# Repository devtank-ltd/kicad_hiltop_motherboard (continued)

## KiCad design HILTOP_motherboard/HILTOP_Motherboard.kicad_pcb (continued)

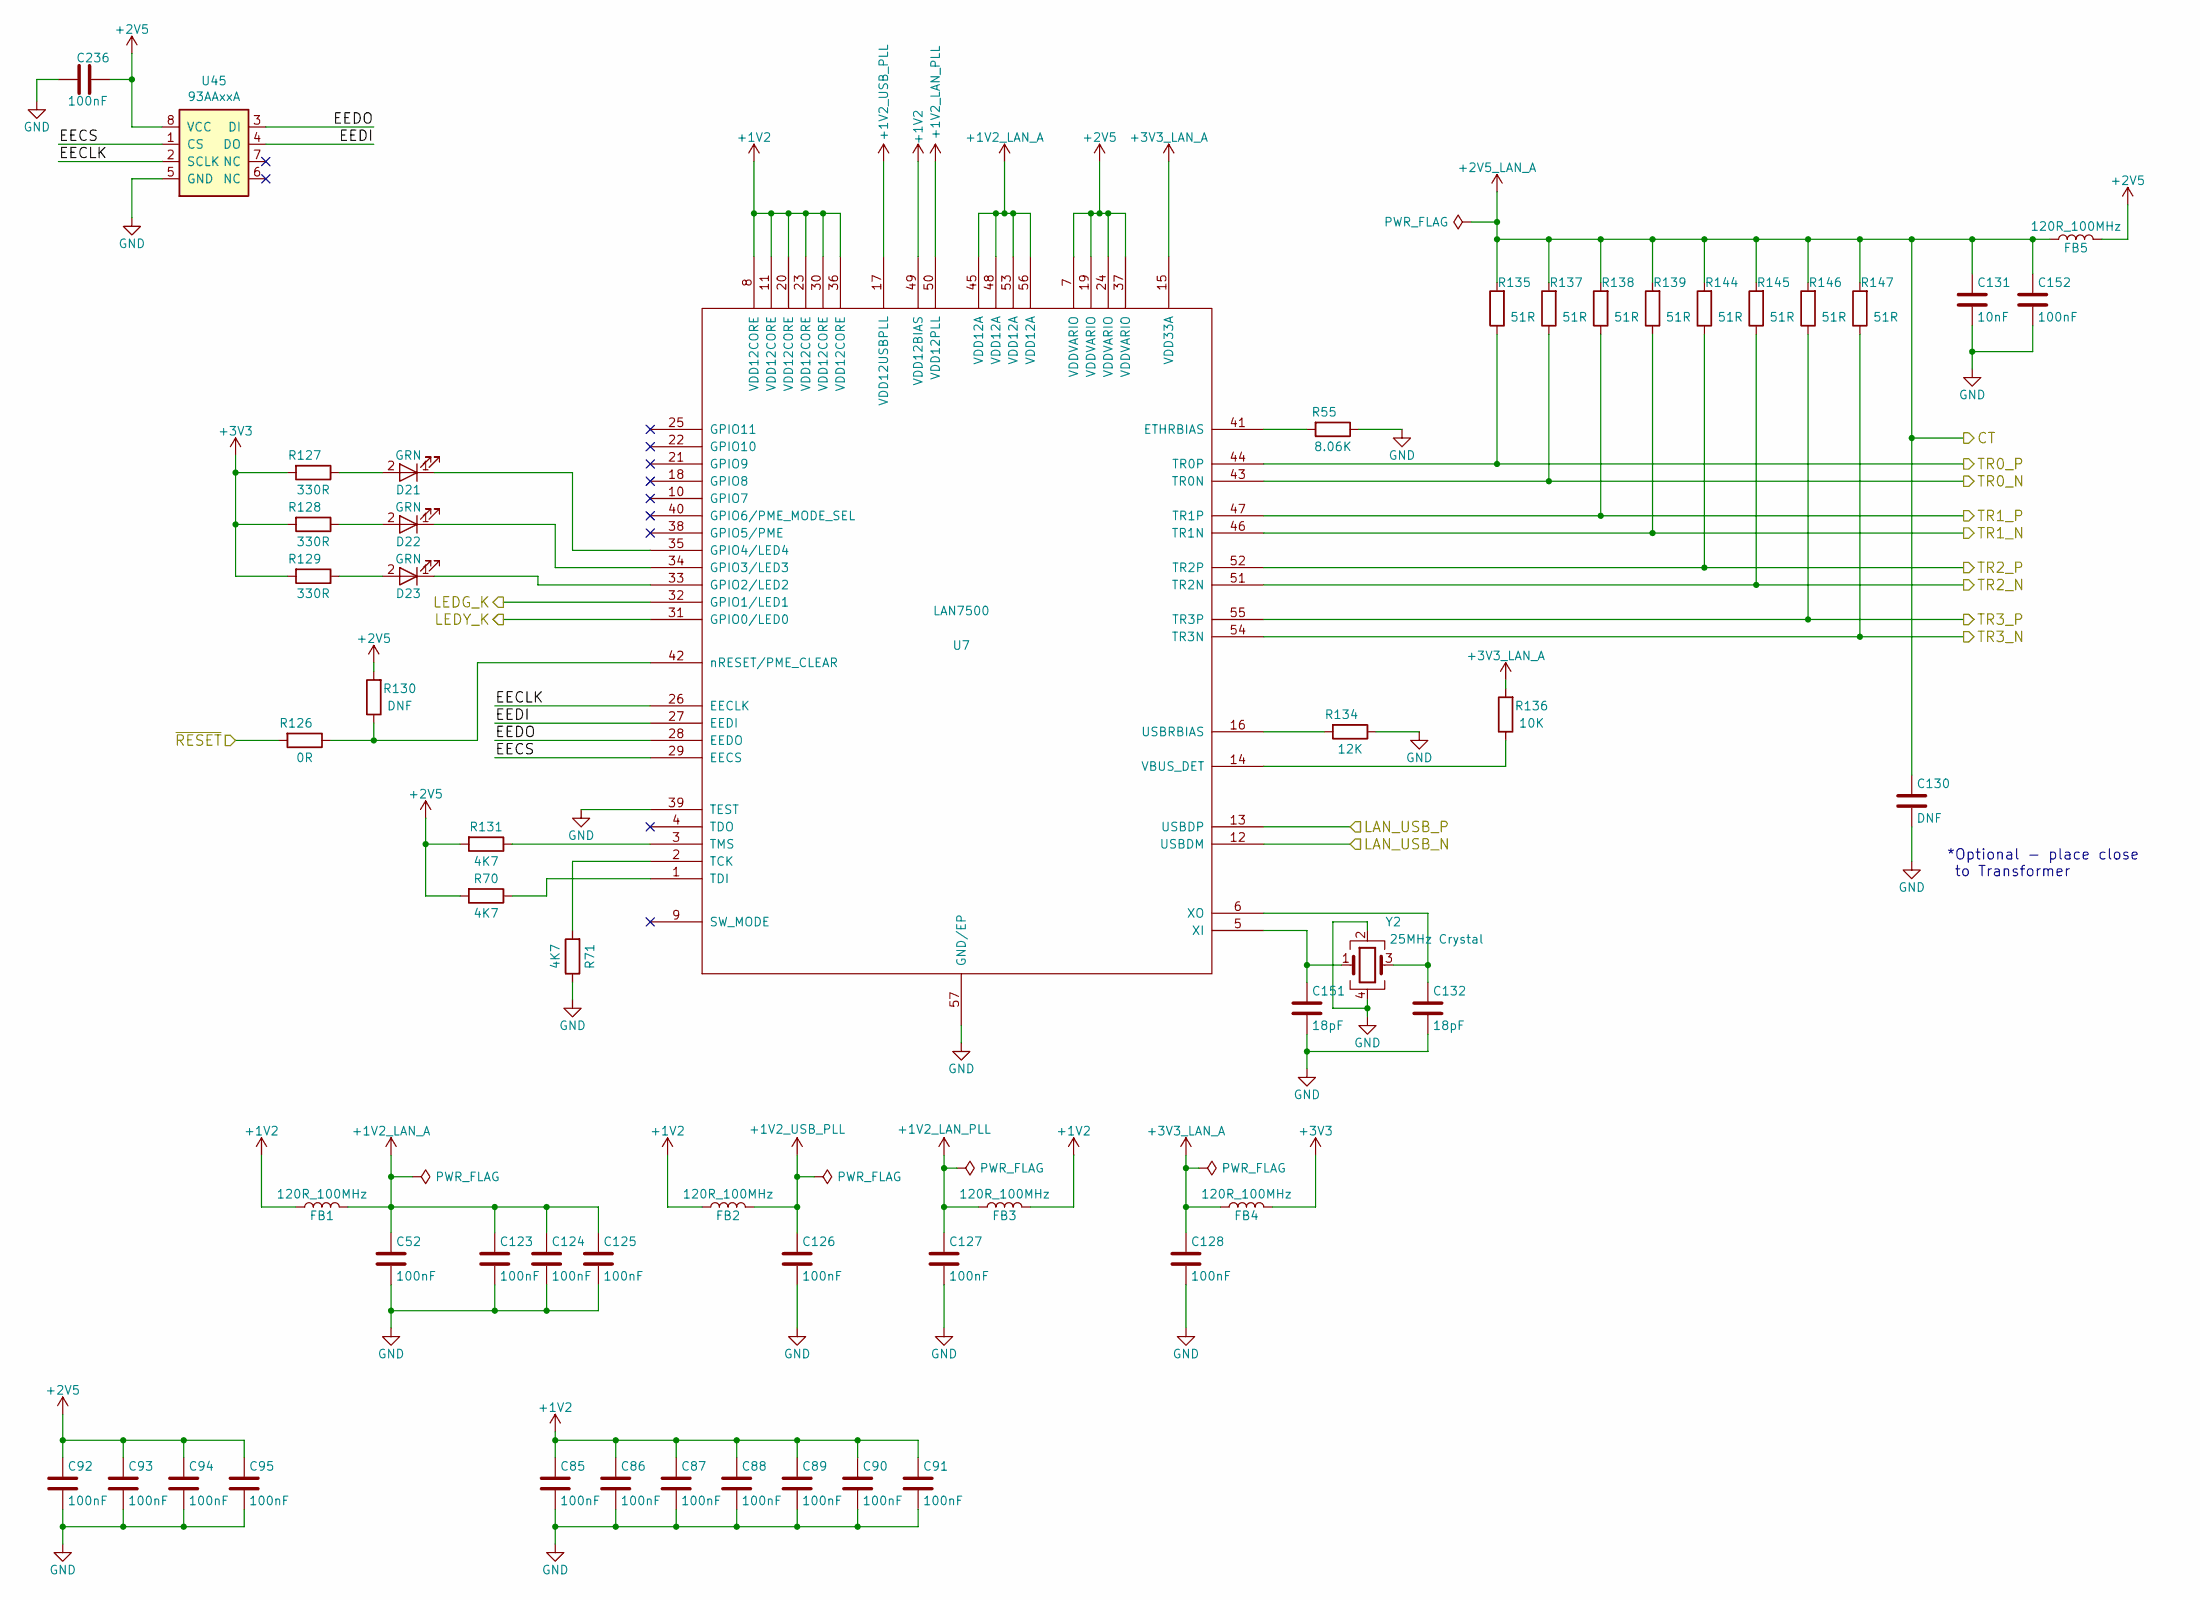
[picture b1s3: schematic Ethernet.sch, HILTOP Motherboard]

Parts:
C52: 100nF; C_0402_1005Metric
C85, C86, C87, C88, C89, C90, C91, C92, C93, C94, C95, C123, C124, C125, C126, C127, C128, C152, C236: 100nF; C_0603_1608Metric
C130: DNF; C_0603_1608Metric
C131: 10nF; C_0603_1608Metric
C132, C151: 18pF; C_0402_1005Metric
D21, D22, D23: GRN; LED_0402_1005Metric
FB1, FB2, FB3, FB4, FB5: 120R_100MHz; R_0603_1608Metric
R55: 8.06K; R_0603_1608Metric
R70, R71, R131: 4K7; R_0603_1608Metric
R126: 0R; R_0603_1608Metric
R127, R128, R129: 330R; R_0603_1608Metric
R130: DNF; R_0603_1608Metric
R134: 12K; R_0603_1608Metric
R135, R137, R138, R139, R144, R145, R146, R147: 51R; R_0603_1608Metric
R136: 10K; R_0603_1608Metric
U7: LAN7500; QFN-56_8x8mm_Pitch0.5mm
U45: 93AAxxA; SOIC-8_3.9x4.9mm_P1.27mm
Y2: 25MHz Crystal; Crystal_SMD_SeikoEpson_FA238V-4Pin_3.2x2.5mm

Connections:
+1V2: C85.1, C86.1, C87.1, C88.1, C89.1, C90.1, C91.1, FB1.1, FB2.1, FB3.2, U7.8 (VDD12CORE), U7.11 (VDD12CORE), U7.20 (VDD12CORE), U7.23 (VDD12CORE), U7.30 (VDD12CORE), U7.36 (VDD12CORE), U7.49 (VDD12BIAS); also elsewhere on the board
+1V2_LAN_A: C52.1, C123.1, C124.1, C125.1, FB1.2, U7.45 (VDD12A), U7.48 (VDD12A), U7.53 (VDD12A), U7.56 (VDD12A)
+1V2_LAN_PLL: C127.1, FB3.1, U7.50 (VDD12PLL)
+1V2_USB_PLL: C126.1, FB2.2, U7.17 (VDD12USBPLL)
+2V5: C92.1, C93.1, C94.1, C95.1, C236.1, FB5.2, R70.2, R130.2, R131.2, U7.7 (VDDVARIO), U7.19 (VDDVARIO), U7.24 (VDDVARIO), U7.37 (VDDVARIO), U45.8 (VCC); also elsewhere on the board
+2V5_LAN_A: C130.1, C131.1, C152.1, FB5.1, R135.2, R137.2, R138.2, R139.2, R144.2, R145.2, R146.2, R147.2; also elsewhere on the board
+3V3: FB4.2, R127.2, R128.2, R129.2; also elsewhere on the board
+3V3_LAN_A: C128.1, FB4.1, R136.2, U7.15 (VDD33A)
/Ethernet/EECLK: U7.26 (EECLK), U45.2 (SCLK)
/Ethernet/EECS: U7.29 (EECS), U45.1 (CS)
/Ethernet/EEDI: U7.27 (EEDI), U45.4 (DO)
/Ethernet/EEDO: U7.28 (EEDO), U45.3 (DI)
/LAN_USB_N: U7.12 (USBDM); also elsewhere on the board
/LAN_USB_P: U7.13 (USBDP); also elsewhere on the board
/LEDG_K: U7.32 (GPIO1/LED1); also elsewhere on the board
/LEDY_K: U7.31 (GPIO0/LED0); also elsewhere on the board
/TR0_N: R137.1, U7.43 (TR0N); also elsewhere on the board
/TR0_P: R135.1, U7.44 (TR0P); also elsewhere on the board
/TR1_N: R139.1, U7.46 (TR1N); also elsewhere on the board
/TR1_P: R138.1, U7.47 (TR1P); also elsewhere on the board
/TR2_N: R145.1, U7.51 (TR2N); also elsewhere on the board
/TR2_P: R144.1, U7.52 (TR2P); also elsewhere on the board
/TR3_N: R147.1, U7.54 (TR3N); also elsewhere on the board
/TR3_P: R146.1, U7.55 (TR3P); also elsewhere on the board
/~MASTER_RESET: R126.2; also elsewhere on the board
GND: C52.2, C85.2, C86.2, C87.2, C88.2, C89.2, C90.2, C91.2, C92.2, C93.2, C94.2, C95.2, C123.2, C124.2, C125.2, C126.2, C127.2, C128.2, C130.2, C131.2, C132.2, C151.2, C152.2, C236.2, R55.1, R71.1, R134.1, U7.39 (TEST), U7.57 (GND/EP), U45.5 (GND), Y2.2, Y2.4; also elsewhere on the board
unnamed: C132.1, U7.6 (XO), Y2.3
unnamed: C151.1, U7.5 (XI), Y2.1
unnamed: D21.1 (K), U7.35 (GPIO4/LED4)
unnamed: D21.2 (A), R127.1
unnamed: D22.1 (K), U7.34 (GPIO3/LED3)
unnamed: D22.2 (A), R128.1
unnamed: D23.1 (K), U7.33 (GPIO2/LED2)
unnamed: D23.2 (A), R129.1
unnamed: R55.2, U7.41 (ETHRBIAS)
unnamed: R70.1, U7.1 (TDI)
unnamed: R71.2, U7.2 (TCK)
unnamed: R126.1, R130.1, U7.42 (nRESET/PME_CLEAR)
unnamed: R131.1, U7.3 (TMS)
unnamed: R134.2, U7.16 (USBRBIAS)
unnamed: R136.1, U7.14 (VBUS_DET)

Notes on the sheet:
*Optional - place close to Transformer

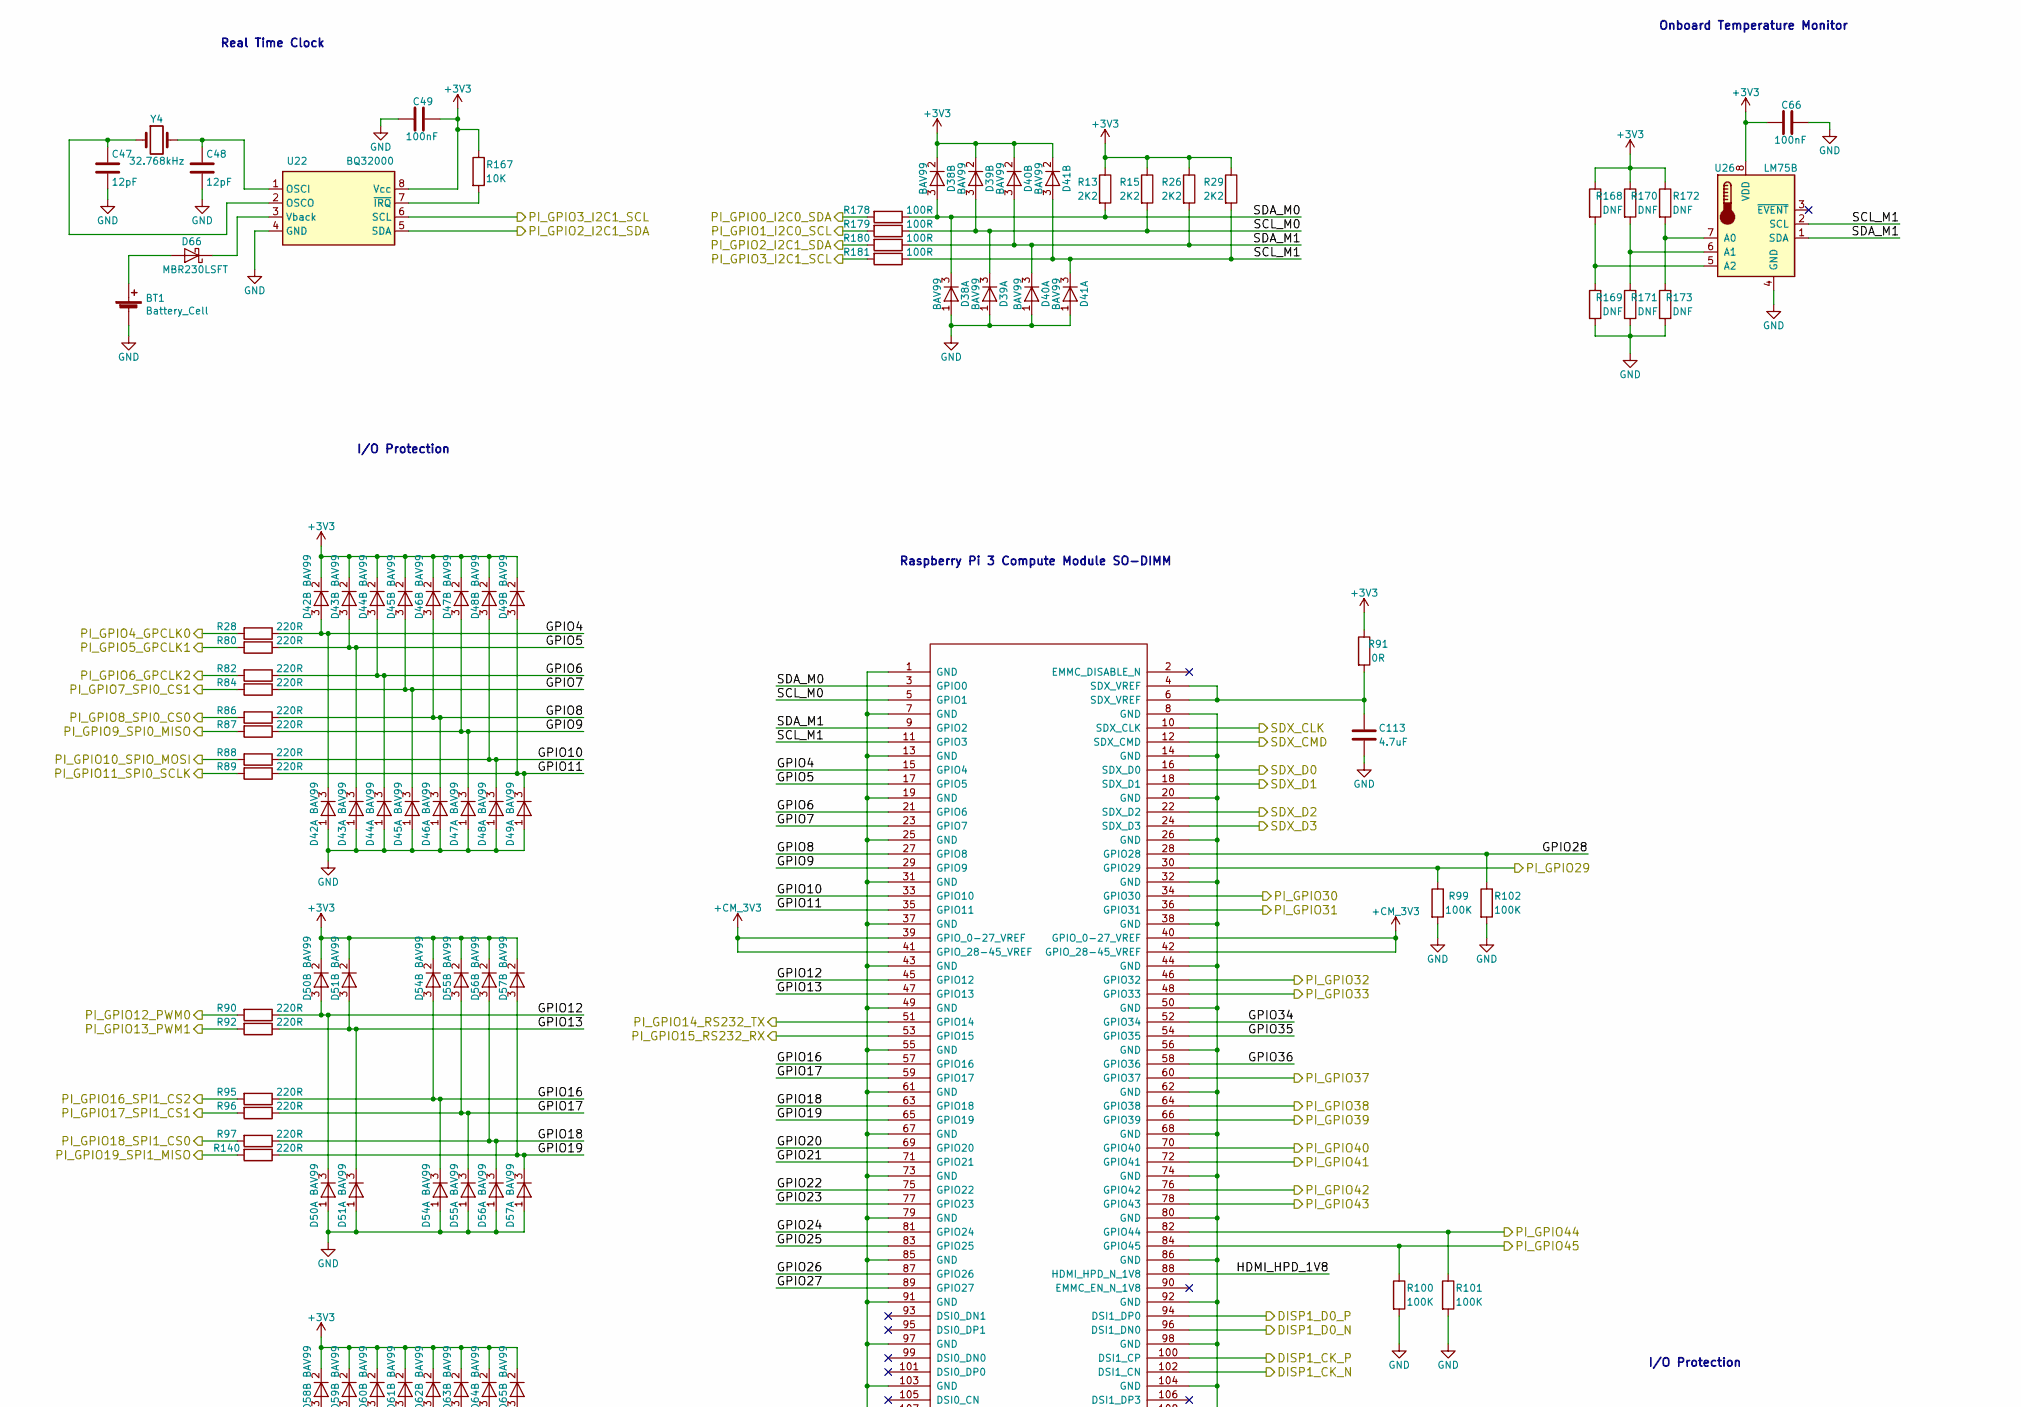
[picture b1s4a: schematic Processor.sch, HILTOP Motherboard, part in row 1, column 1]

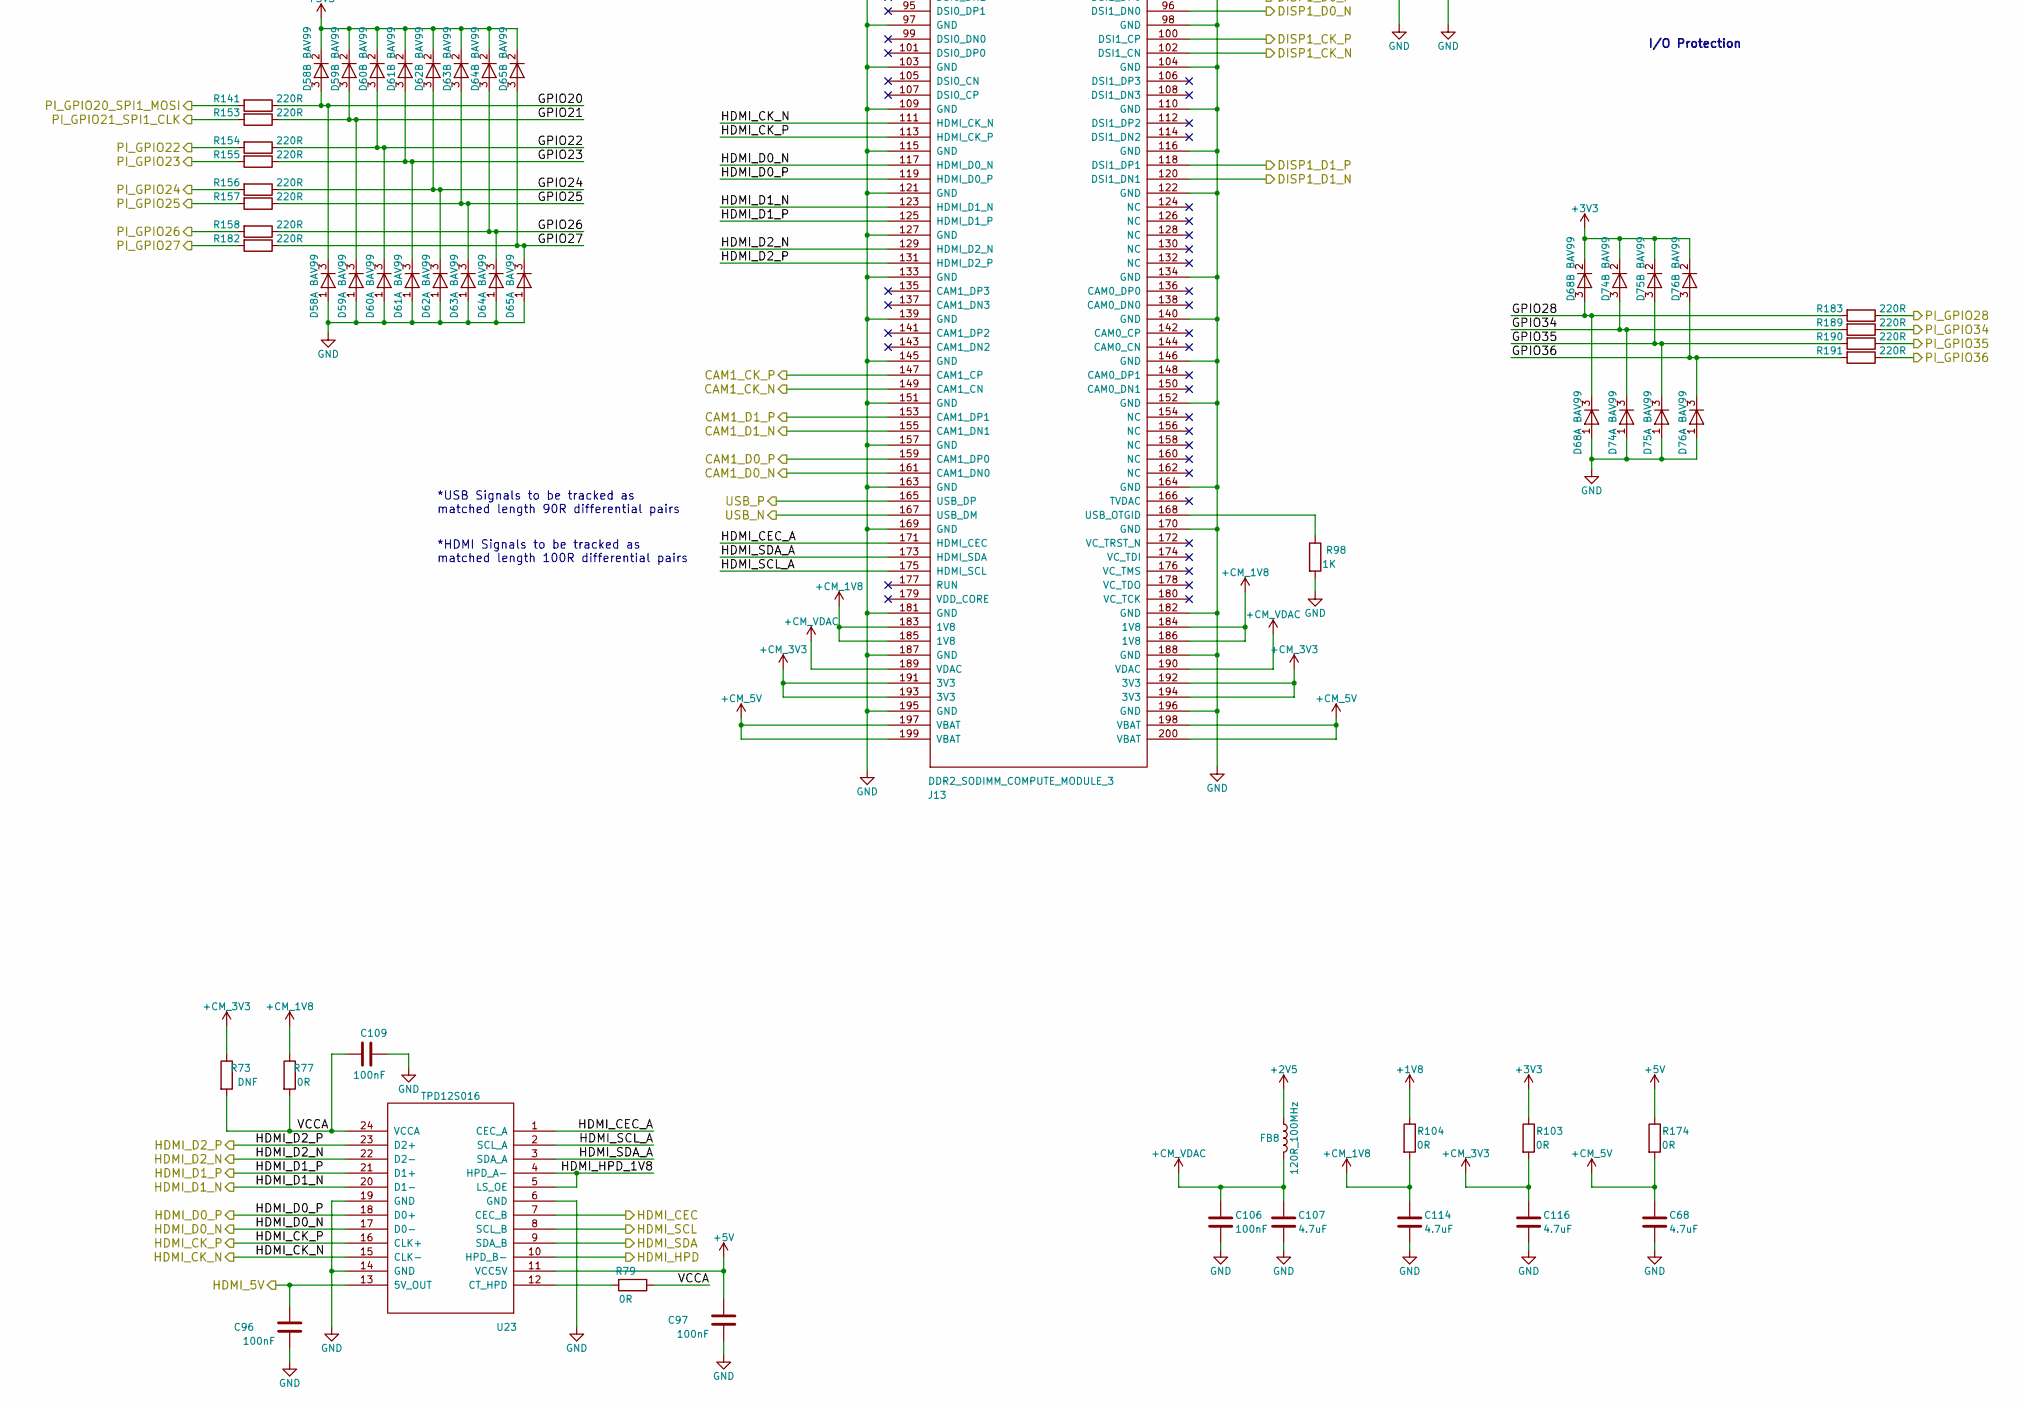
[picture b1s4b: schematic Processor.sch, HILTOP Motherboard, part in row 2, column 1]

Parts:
BT1: Battery_Cell; BatteryHolder_Keystone_1061_1x20mm
C47, C48: 12pF; C_0603_1608Metric
C49, C66, C96, C97, C106, C109: 100nF; C_0603_1608Metric
C68, C107, C113, C114, C116: 4.7uF; C_0805_2012Metric
D38, D39, D40, D41, D42, D43, D44, D45, D46, D47, D48, D49, D50, D51, D54, D55, D56, D57, D58, D59, D60, D61, D62, D63, D64, D65, D68, D74, D75, D76: BAV99; SOT-23
D66: MBR230LSFT; D_SOD-123F
FB8: 120R_100MHz; R_0603_1608Metric
J13: DDR2_SODIMM_COMPUTE_MODULE_3; Conn_TE-DDR2-SODIMM-0.6-200P-ComputeModule
R13, R15, R26, R29: 2K2; R_0603_1608Metric
R28, R80, R82, R84, R86, R87, R88, R89, R90, R92, R95, R96, R97, R140, R141, R153, R154, R155, R156, R157, R158, R182, R183, R189, R190, R191: 220R; R_0402_1005Metric
R73: DNF; R_0603_1608Metric
R77, R79, R91, R103, R104, R174: 0R; R_0603_1608Metric
R98: 1K; R_0603_1608Metric
R99, R100, R101, R102: 100K; R_0402_1005Metric
R167: 10K; R_0603_1608Metric
R168, R169, R170, R171, R172, R173: DNF; R_0402_1005Metric
R178, R179, R180, R181: 100R; R_0402_1005Metric
U22: BQ32000; SOIC-8_3.9x4.9mm_P1.27mm
U23: TPD12S016; TSSOP-24_4.4x7.8mm_P0.65mm
U26: LM75B; SOIC-8_3.9x4.9mm_P1.27mm
Y4: 32.768kHz; Crystal_SMD_EuroQuartz_EQ161-2Pin_3.2x1.5mm

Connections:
+1V8: R104.1; also elsewhere on the board
+2V5: FB8.1; also elsewhere on the board
+3V3: C49.1, C66.2, D38.2 (K), D39.2 (K), D40.2 (K), D41.2 (K), D42.2 (K), D43.2 (K), D44.2 (K), D45.2 (K), D46.2 (K), D47.2 (K), D48.2 (K), D49.2 (K), D50.2 (K), D51.2 (K), D54.2 (K), D55.2 (K), D56.2 (K), D57.2 (K), D58.2 (K), D59.2 (K), D60.2 (K), D61.2 (K), D62.2 (K), D63.2 (K), D64.2 (K), D65.2 (K), D68.2 (K), D74.2 (K), D75.2 (K), D76.2 (K), R13.1, R15.1, R26.1, R29.1, R91.1, R103.1, R167.1, R168.1, R170.1, R172.1, U22.8 (Vcc), U26.8 (VDD); also elsewhere on the board
+CM_1V8: C114.1, J13.183 (1V8), J13.184 (1V8), J13.185 (1V8), J13.186 (1V8), R77.1, R104.2
+CM_3V3: C116.1, J13.39 (GPIO_0-27_VREF), J13.40 (GPIO_0-27_VREF), J13.41 (GPIO_28-45_VREF), J13.42 (GPIO_28-45_VREF), J13.191 (3V3), J13.192 (3V3), J13.193 (3V3), J13.194 (3V3), R73.1, R103.2
+CM_5V: C68.1, J13.197 (VBAT), J13.198 (VBAT), J13.199 (VBAT), J13.200 (VBAT), R174.2
+CM_VDAC: C106.1, C107.1, FB8.2, J13.189 (VDAC), J13.190 (VDAC)
/ATX_PWR_SHDN: J13.84 (GPIO45), R100.1; also elsewhere on the board
/BCK_SHUTDOWN: J13.36 (GPIO31); also elsewhere on the board
/CAM1_CK_N: J13.149 (CAM1_CN); also elsewhere on the board
/CAM1_CK_P: J13.147 (CAM1_CP); also elsewhere on the board
/CAM1_D0_N: J13.161 (CAM1_DN0); also elsewhere on the board
/CAM1_D0_P: J13.159 (CAM1_DP0); also elsewhere on the board
/CAM1_D1_N: J13.155 (CAM1_DN1); also elsewhere on the board
/CAM1_D1_P: J13.153 (CAM1_DP1); also elsewhere on the board
/CAN_CH1_CS: J13.70 (GPIO40); also elsewhere on the board
/CAN_CH2_CS: J13.72 (GPIO41); also elsewhere on the board
/DC_DC_ENABLE: J13.60 (GPIO37); also elsewhere on the board
/DC_OUT_ENABLE: J13.82 (GPIO44), R101.1; also elsewhere on the board
/DEBUG_RX: J13.53 (GPIO15); also elsewhere on the board
/DEBUG_TX: J13.51 (GPIO14); also elsewhere on the board
/DISP1_CK_N: J13.102 (DSI1_CN); also elsewhere on the board
/DISP1_CK_P: J13.100 (DSI1_CP); also elsewhere on the board
/DISP1_D0_N: J13.96 (DSI1_DN0); also elsewhere on the board
/DISP1_D0_P: J13.94 (DSI1_DP0); also elsewhere on the board
/DISP1_D1_N: J13.120 (DSI1_DN1); also elsewhere on the board
/DISP1_D1_P: J13.118 (DSI1_DP1); also elsewhere on the board
/EXT_TEMP_1WIRE: J13.34 (GPIO30); also elsewhere on the board
/FAN_SENSE_1: J13.46 (GPIO32); also elsewhere on the board
/FAN_SENSE_2: J13.48 (GPIO33); also elsewhere on the board
/I2C0_SCL: R179.2; also elsewhere on the board
/I2C0_SDA: R178.2; also elsewhere on the board
/I2C1_SCL: R181.2, U22.6 (SCL); also elsewhere on the board
/I2C1_SDA: R180.2, U22.5 (SDA); also elsewhere on the board
/MCP23017_INTA: J13.76 (GPIO42); also elsewhere on the board
/MCP23017_INTB: J13.78 (GPIO43); also elsewhere on the board
/PR_GPIO22: R154.2; also elsewhere on the board
/PR_GPIO23: R155.2; also elsewhere on the board
/PR_GPIO24: R156.2; also elsewhere on the board
/PR_GPIO25: R157.2; also elsewhere on the board
/PR_GPIO26: R158.2; also elsewhere on the board
/PR_GPIO27: R182.2; also elsewhere on the board
/PR_GPIO28: R183.1; also elsewhere on the board
/PR_GPIO34: R189.1; also elsewhere on the board
/PR_GPIO35: R190.1; also elsewhere on the board
/PR_GPIO36: R191.1; also elsewhere on the board
/Processor/GPIO4: D42.3 (K), J13.15 (GPIO4), R28.1
/Processor/GPIO5: D43.3 (K), J13.17 (GPIO5), R80.1
/Processor/GPIO6: D44.3 (K), J13.21 (GPIO6), R82.1
/Processor/GPIO7: D45.3 (K), J13.23 (GPIO7), R84.1
/Processor/GPIO8: D46.3 (K), J13.27 (GPIO8), R86.1
/Processor/GPIO9: D47.3 (K), J13.29 (GPIO9), R87.1
/Processor/GPIO10: D48.3 (K), J13.33 (GPIO10), R88.1
/Processor/GPIO11: D49.3 (K), J13.35 (GPIO11), R89.1
/Processor/GPIO12: D50.3 (K), J13.45 (GPIO12), R90.1
/Processor/GPIO13: D51.3 (K), J13.47 (GPIO13), R92.1
/Processor/GPIO16: D54.3 (K), J13.57 (GPIO16), R95.1
/Processor/GPIO17: D55.3 (K), J13.59 (GPIO17), R96.1
/Processor/GPIO18: D56.3 (K), J13.63 (GPIO18), R97.1
/Processor/GPIO19: D57.3 (K), J13.65 (GPIO19), R140.1
/Processor/GPIO20: D58.3 (K), J13.69 (GPIO20), R141.1
/Processor/GPIO21: D59.3 (K), J13.71 (GPIO21), R153.1
/Processor/GPIO22: D60.3 (K), J13.75 (GPIO22), R154.1
/Processor/GPIO23: D61.3 (K), J13.77 (GPIO23), R155.1
/Processor/GPIO24: D62.3 (K), J13.81 (GPIO24), R156.1
/Processor/GPIO25: D63.3 (K), J13.83 (GPIO25), R157.1
/Processor/GPIO26: D64.3 (K), J13.87 (GPIO26), R158.1
/Processor/GPIO27: D65.3 (K), J13.89 (GPIO27), R182.1
/Processor/GPIO28: D68.3 (K), J13.28 (GPIO28), R102.1, R183.2
/Processor/GPIO34: D74.3 (K), J13.52 (GPIO34), R189.2
/Processor/GPIO35: D75.3 (K), J13.54 (GPIO35), R190.2
/Processor/GPIO36: D76.3 (K), J13.58 (GPIO36), R191.2
/Processor/HDMI_5V: C96.2, U23.13 (5V_OUT); also elsewhere on the board
/Processor/HDMI_CEC: U23.7 (CEC_B); also elsewhere on the board
/Processor/HDMI_CEC_A: J13.171 (HDMI_CEC), U23.1 (CEC_A)
/Processor/HDMI_CK_N: J13.111 (HDMI_CK_N), U23.15 (CLK-); also elsewhere on the board
/Processor/HDMI_CK_P: J13.113 (HDMI_CK_P), U23.16 (CLK+); also elsewhere on the board
/Processor/HDMI_D0_N: J13.117 (HDMI_D0_N), U23.17 (D0-); also elsewhere on the board
/Processor/HDMI_D0_P: J13.119 (HDMI_D0_P), U23.18 (D0+); also elsewhere on the board
/Processor/HDMI_D1_N: J13.123 (HDMI_D1_N), U23.20 (D1-); also elsewhere on the board
/Processor/HDMI_D1_P: J13.125 (HDMI_D1_P), U23.21 (D1+); also elsewhere on the board
/Processor/HDMI_D2_N: J13.129 (HDMI_D2_N), U23.22 (D2-); also elsewhere on the board
/Processor/HDMI_D2_P: J13.131 (HDMI_D2_P), U23.23 (D2+); also elsewhere on the board
/Processor/HDMI_HPD: U23.10 (HPD_B-); also elsewhere on the board
/Processor/HDMI_HPD_1V8: J13.88 (HDMI_HPD_N_1V8), U23.4 (HPD_A-), U23.5 (LS_OE)
/Processor/HDMI_SCL: U23.8 (SCL_B); also elsewhere on the board
/Processor/HDMI_SCL_A: J13.175 (HDMI_SCL), U23.2 (SCL_A)
/Processor/HDMI_SDA: U23.9 (SDA_B); also elsewhere on the board
/Processor/HDMI_SDA_A: J13.173 (HDMI_SDA), U23.3 (SDA_A)
/Processor/PI_GPIO13_PWM1: R92.2; also elsewhere on the board
/Processor/SCL_M0: D39.3 (K), J13.5 (GPIO1), R15.2, R179.1
/Processor/SCL_M1: D41.3 (K), J13.11 (GPIO3), R29.2, R181.1, U26.2 (SCL)
/Processor/SDA_M0: D38.3 (K), J13.3 (GPIO0), R13.2, R178.1
/Processor/SDA_M1: D40.3 (K), J13.9 (GPIO2), R26.2, R180.1, U26.1 (SDA)
/Processor/SDX_CLK: J13.10 (SDX_CLK); also elsewhere on the board
/Processor/SDX_CMD: J13.12 (SDX_CMD); also elsewhere on the board
/Processor/SDX_D0: J13.16 (SDX_D0); also elsewhere on the board
/Processor/SDX_D1: J13.18 (SDX_D1); also elsewhere on the board
/Processor/SDX_D2: J13.22 (SDX_D2); also elsewhere on the board
/Processor/SDX_D3: J13.24 (SDX_D3); also elsewhere on the board
/Processor/VCCA: C109.2, R73.2, R77.2, R79.1, U23.24 (VCCA)
/SPI0_CS0: R86.2; also elsewhere on the board
/SPI0_CS1: R84.2; also elsewhere on the board
/SPI0_MISO: R87.2; also elsewhere on the board
/SPI0_MOSI: R88.2; also elsewhere on the board
/SPI0_SCLK: R89.2; also elsewhere on the board
/SPI1_CS0: R97.2; also elsewhere on the board
/SPI1_CS1_CAM_IO0: R96.2; also elsewhere on the board
/SPI1_CS2_CAM_IO1: R95.2; also elsewhere on the board
/SPI1_MISO: R140.2; also elsewhere on the board
/SPI1_MOSI: R141.2; also elsewhere on the board
/SPI1_SCLK: R153.2; also elsewhere on the board
/SYS_CLK0: R28.2; also elsewhere on the board
/SYS_CLK1: R80.2; also elsewhere on the board
/SYS_FAN_DC: J13.30 (GPIO29), R99.1; also elsewhere on the board
/SYS_PWM0: R90.2; also elsewhere on the board
/SYS_TRIG: R82.2; also elsewhere on the board
/UART_CH1_CS: J13.64 (GPIO38); also elsewhere on the board
/UART_CH2_CS: J13.66 (GPIO39); also elsewhere on the board
/USB_ROOT_N: J13.167 (USB_DM); also elsewhere on the board
/USB_ROOT_P: J13.165 (USB_DP); also elsewhere on the board
GND: BT1.2 (-), C47.2, C48.2, C49.2, C66.1, C68.2, C96.1, C97.1, C106.2, C107.2, C109.1, C113.2, C114.2, C116.2, D38.1 (A), D39.1 (A), D40.1 (A), D41.1 (A), D42.1 (A), D43.1 (A), D44.1 (A), D45.1 (A), D46.1 (A), D47.1 (A), D48.1 (A), D49.1 (A), D50.1 (A), D51.1 (A), D54.1 (A), D55.1 (A), D56.1 (A), D57.1 (A), D58.1 (A), D59.1 (A), D60.1 (A), D61.1 (A), D62.1 (A), D63.1 (A), D64.1 (A), D65.1 (A), D68.1 (A), D74.1 (A), D75.1 (A), D76.1 (A), J13.1 (GND), J13.7 (GND), J13.8 (GND), J13.13 (GND), J13.14 (GND), J13.19 (GND), J13.20 (GND), J13.25 (GND), J13.26 (GND), J13.31 (GND), J13.32 (GND), J13.37 (GND), J13.38 (GND), J13.43 (GND), J13.44 (GND), J13.49 (GND), J13.50 (GND), J13.55 (GND), J13.56 (GND), J13.61 (GND), J13.62 (GND), J13.67 (GND), J13.68 (GND), J13.73 (GND), J13.74 (GND), J13.79 (GND), J13.80 (GND), J13.85 (GND), J13.86 (GND), J13.91 (GND), J13.92 (GND), J13.97 (GND), J13.98 (GND), J13.103 (GND), J13.104 (GND), J13.109 (GND), J13.110 (GND), J13.115 (GND), J13.116 (GND), J13.121 (GND), J13.122 (GND), J13.127 (GND), J13.133 (GND), J13.134 (GND), J13.139 (GND), J13.140 (GND), J13.145 (GND), J13.146 (GND), J13.151 (GND), J13.152 (GND), J13.157 (GND), J13.163 (GND), J13.164 (GND), J13.169 (GND), J13.170 (GND), J13.181 (GND), J13.182 (GND), J13.187 (GND), J13.188 (GND), J13.195 (GND), J13.196 (GND), R98.2, R99.2, R100.2, R101.2, R102.2, R169.2, R171.2, R173.2, U22.4 (GND), U23.6 (GND), U23.14 (GND), U23.19 (GND), U26.4 (GND); also elsewhere on the board
unnamed: BT1.1 (+), D66.2 (A)
unnamed: C47.1, U22.2 (OSCO), Y4.1
unnamed: C48.1, U22.1 (OSCI), Y4.2
unnamed: C113.1, J13.4 (SDX_VREF), J13.6 (SDX_VREF), R91.2
unnamed: D66.1 (K), U22.3 (Vback)
unnamed: J13.168 (USB_OTGID), R98.1
unnamed: R79.2, U23.12 (CT_HPD)
unnamed: R167.2, U22.7 (~IRQ)
unnamed: R168.2, R169.1, U26.5 (A2)
unnamed: R170.2, R171.1, U26.6 (A1)
unnamed: R172.2, R173.1, U26.7 (A0)

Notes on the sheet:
*USB Signals to be tracked as matched length 90R differential pairs
*HDMI Signals to be tracked as matched length 100R differential pairs
I/O Protection
Raspberry Pi 3 Compute Module SO-DIMM
Real Time Clock
Onboard Temperature Monitor

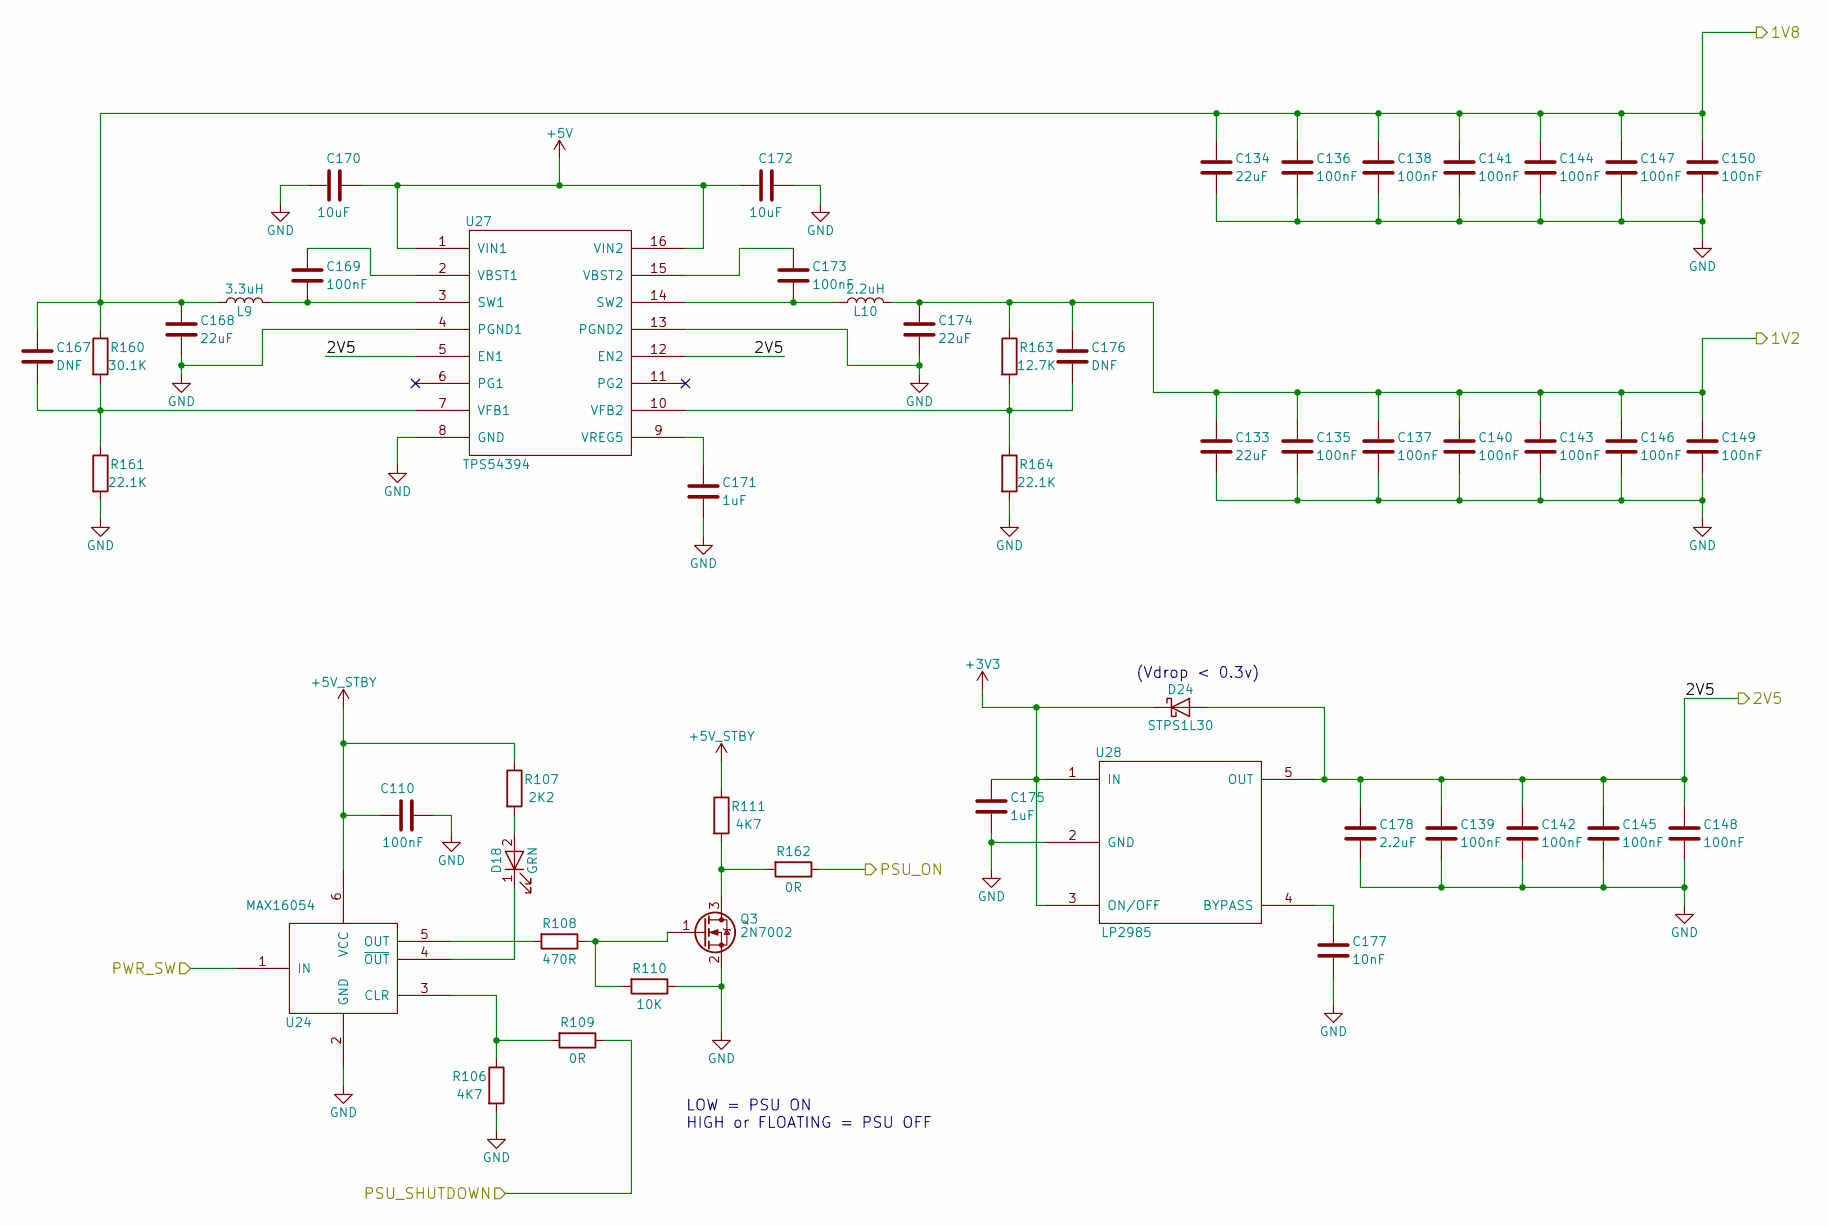
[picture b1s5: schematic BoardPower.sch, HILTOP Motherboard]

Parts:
C110, C135, C136, C137, C138, C139, C140, C141, C142, C143, C144, C145, C146, C147, C148, C149, C150, C169, C173: 100nF; C_0603_1608Metric
C133, C134, C168, C174: 22uF; C_1206_3216Metric
C167, C176: DNF; C_0603_1608Metric
C170, C172: 10uF; C_0805_2012Metric
C171: 1uF; C_0805_2012Metric
C175: 1uF; C_0603_1608Metric
C177: 10nF; C_0603_1608Metric
C178: 2.2uF; C_0805_2012Metric
D18: GRN; LED_0402_1005Metric
D24: STPS1L30; D_SMB
L9: 3.3uH; Inductor_8x8
L10: 2.2uH; Inductor_8x8
Q3: 2N7002; SOT-23
R106, R111: 4K7; R_0603_1608Metric
R107: 2K2; R_0603_1608Metric
R108: 470R; R_0603_1608Metric
R109, R162: 0R; R_0603_1608Metric
R110: 10K; R_0603_1608Metric
R160: 30.1K; R_0603_1608Metric
R161, R164: 22.1K; R_0603_1608Metric
R163: 12.7K; R_0603_1608Metric
U24: MAX16054; TSOT-23-6
U27: TPS54394; HTSSOP-16_4.4x5mm_Pitch0.65mm
U28: LP2985; SOT-23-5

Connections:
+1V2: C133.1, C135.1, C137.1, C140.1, C143.1, C146.1, C149.1, C174.1, C176.1, L10.2, R163.1; also elsewhere on the board
+1V8: C134.1, C136.1, C138.1, C141.1, C144.1, C147.1, C150.1, C167.1, C168.1, L9.1, R160.1; also elsewhere on the board
+2V5: C139.1, C142.1, C145.1, C148.1, C178.1, D24.2 (A), U27.5 (EN1), U27.12 (EN2), U28.5 (OUT); also elsewhere on the board
+3V3: C175.1, D24.1 (K), U28.1 (IN), U28.3 (ON/OFF); also elsewhere on the board
+5V_STBY: C110.1, R107.1, R111.1, U24.6 (VCC); also elsewhere on the board
/ATX_PWR_SHDN: R109.1; also elsewhere on the board
/BoardPower/PSU_ON: R162.1; also elsewhere on the board
/PWR_SW: U24.1 (IN); also elsewhere on the board
GND: C110.2, C133.2, C134.2, C135.2, C136.2, C137.2, C138.2, C139.2, C140.2, C141.2, C142.2, C143.2, C144.2, C145.2, C146.2, C147.2, C148.2, C149.2, C150.2, C168.2, C170.2, C171.2, C172.1, C174.2, C175.2, C177.2, C178.2, Q3.2 (S), R106.2, R110.1, R161.2, R164.2, U24.2 (GND), U27.4 (PGND1), U27.8 (GND), U27.13 (PGND2), U28.2 (GND); also elsewhere on the board
unnamed: C167.2, R160.2, R161.1, U27.7 (VFB1)
unnamed: C169.1, U27.2 (VBST1)
unnamed: C169.2, L9.2, U27.3 (SW1)
unnamed: C171.1, U27.9 (VREG5)
unnamed: C173.1, U27.15 (VBST2)
unnamed: C173.2, L10.1, U27.14 (SW2)
unnamed: C176.2, R163.2, R164.1, U27.10 (VFB2)
unnamed: C177.1, U28.4 (BYPASS)
unnamed: D18.1 (K), U24.4 (~OUT)
unnamed: D18.2 (A), R107.2
unnamed: Q3.1 (G), R108.1, R110.2
unnamed: Q3.3 (D), R111.2, R162.2
unnamed: R106.1, R109.2, U24.3 (CLR)
unnamed: R108.2, U24.5 (OUT)

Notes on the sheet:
LOW = PSU ON HIGH or FLOATING = PSU OFF
(Vdrop < 0.3v)
